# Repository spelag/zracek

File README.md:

# zracek

Spoznajte Zraček – obesek za ključe, ki vam z enim samim pogledom razkrije trenutno kakovost zraka v vaši okolici in 12-urno napoved. Zasnovan je za vse: od tistih, ki jim sodobna tehnologija ni najbližja, do uporabnikov, ki cenijo hitre in preproste rešitve v vsakdanjem življenju. Uporabljate raje pametno uro? Z obrazom za uro Zraček imate podatke vedno na zapestju. Na naši spletni strani pa lahko preverite tudi, kje v okolici so nove merilne postaje najbolj nujne, glede na dejavnike kot so bližina vrtcov, šol in bolnišnic, ter števila uporabnikov Zračka.

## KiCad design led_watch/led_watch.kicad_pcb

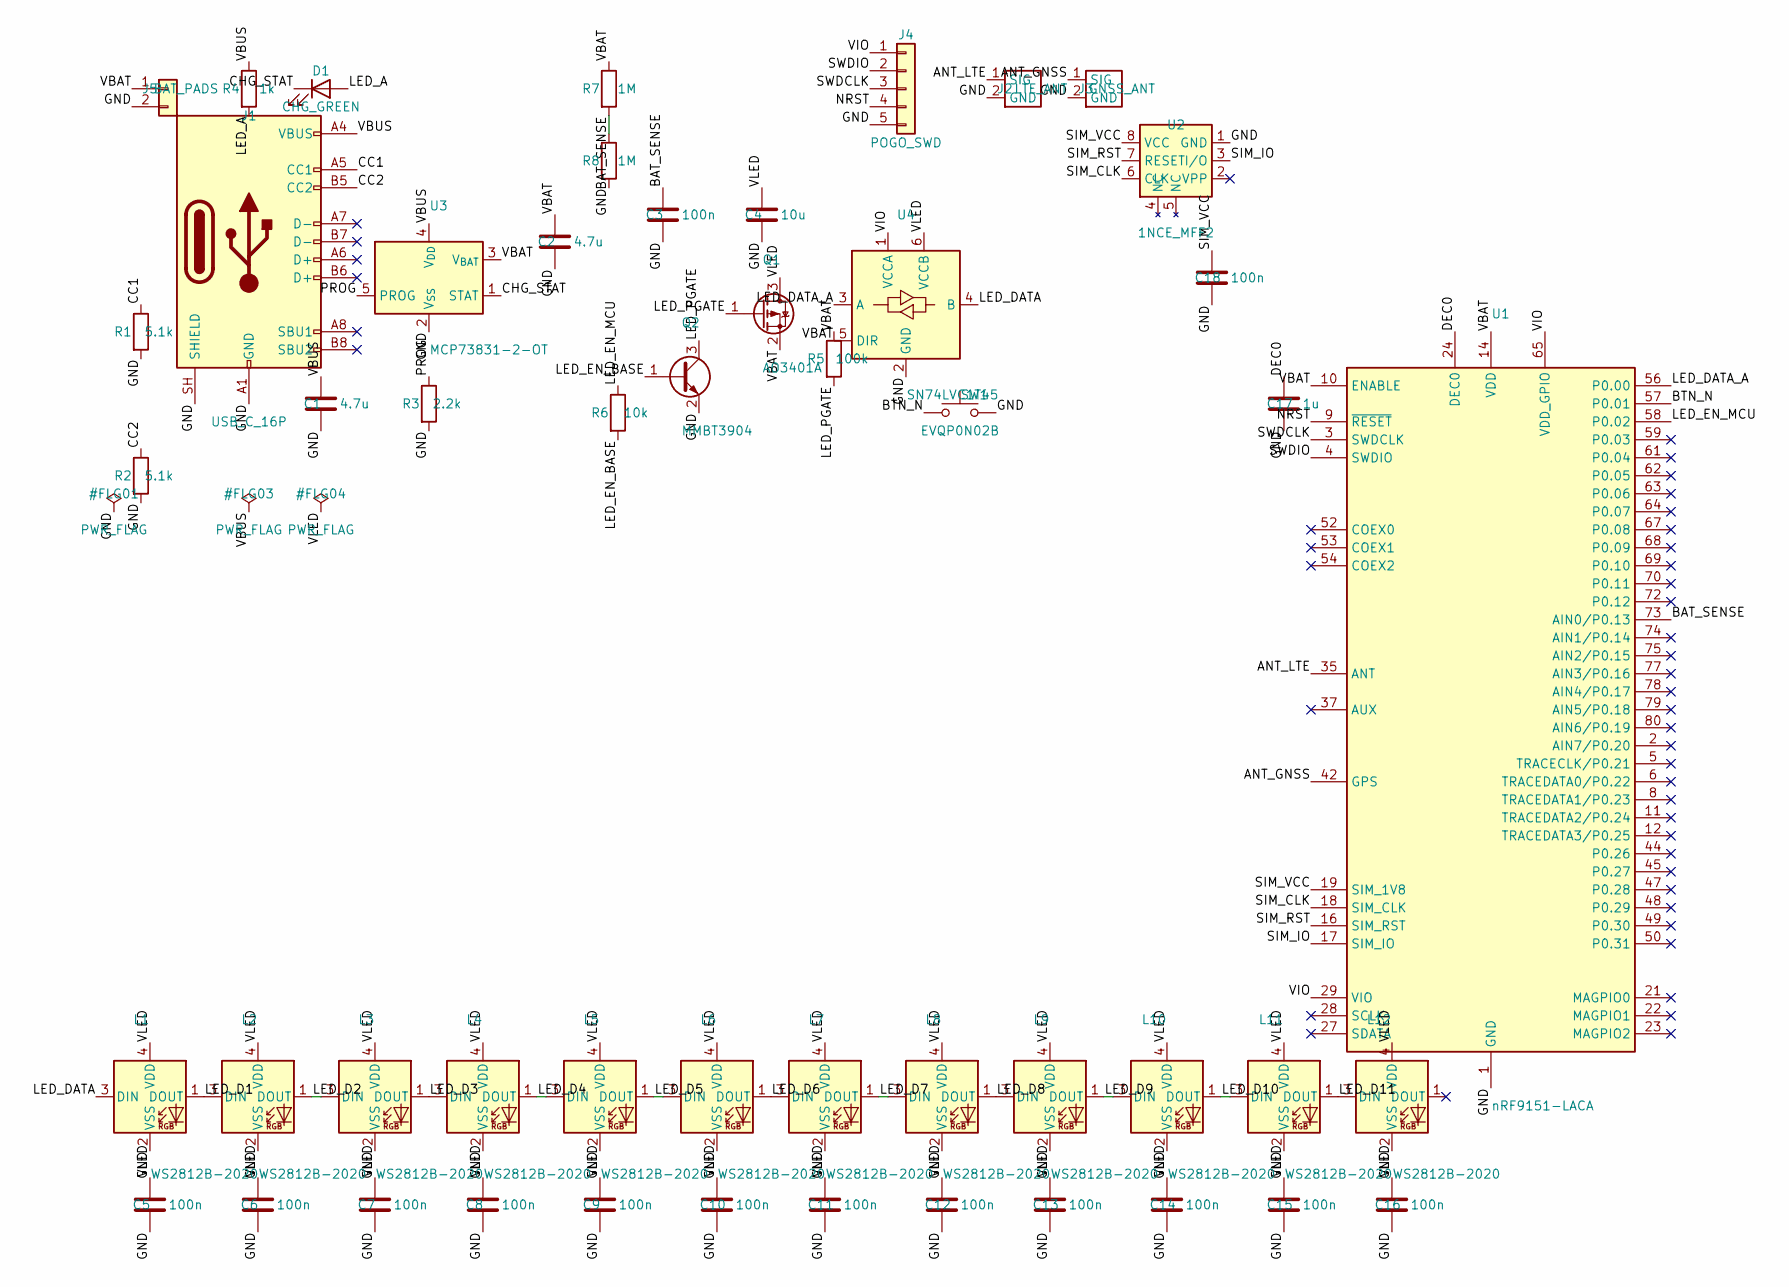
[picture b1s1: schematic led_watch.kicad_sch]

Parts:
C1, C2: 4.7u; C_0603_1608Metric
C3, C5, C6, C7, C8, C9, C10, C11, C12, C13, C14, C15, C16, C18: 100n; C_0402_1005Metric
C4: 10u; C_0603_1608Metric
C17: 1u; C_0402_1005Metric
D1: CHG_GREEN; LED_0603_1608Metric
J1: USB_C_16P; USB_C_Receptacle_HRO_TYPE-C-31-M-12
J2: LTE_ANT; U.FL_Hirose_U.FL-R-SMT-1_Vertical
J3: GNSS_ANT; U.FL_Hirose_U.FL-R-SMT-1_Vertical
J4: POGO_SWD; TestPads_1x05_P1.27mm
J5: BAT_PADS; BatteryPads_2P_P3.0mm
L1, L2, L3, L4, L5, L6, L7, L8, L9, L10, L11, L12: WS2812B-2020; LED_WS2812B-2020_PLCC4_2.0x2.0mm
Q1: AO3401A; SOT-23
Q2: MMBT3904; SOT-23
R1, R2: 5.1k; R_0402_1005Metric
R3: 2.2k; R_0402_1005Metric
R4: 1k; R_0402_1005Metric
R5: 100k; R_0402_1005Metric
R6: 10k; R_0402_1005Metric
R7, R8: 1M; R_0402_1005Metric
SW1: EVQP0N02B; SW_SPST_EVQP0
U1: nRF9151-LACA; Nordic_nRF9151-LAxx_LGA-80-33EP_12.1x11.1mm_P0.5mm
U2: 1NCE_MFF2; MFF2_eSIM
U3: MCP73831-2-OT; SOT-23-5
U4: SN74LVC1T45; SOT-23-6

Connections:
/ANT_GNSS: J3.1 (SIG), U1.42 (GPS)
/ANT_LTE: J2.1 (SIG), U1.35 (ANT)
/BAT_SENSE: C3.1, R7.2, R8.1, U1.73 (AIN0/P0.13)
/BTN_N: SW1.1, U1.57 (P0.01)
/CC1: J1.A5 (CC1), R1.1
/CC2: J1.B5 (CC2), R2.1
/CHG_STAT: D1.1 (K), U3.1 (STAT)
/DEC0: C17.1, U1.24 (DEC0)
/GND: C1.2, C2.2, C3.2, C4.2, C5.2, C6.2, C7.2, C8.2, C9.2, C10.2, C11.2, C12.2, C13.2, C14.2, C15.2, C16.2, C17.2, C18.2, J1.A1 (GND), J1.A12 (GND), J1.B1 (GND), J1.B12 (GND), J1.SH (SHIELD), J2.2 (GND), J3.2 (GND), J4.5, J5.2, L1.2 (VSS), L2.2 (VSS), L3.2 (VSS), L4.2 (VSS), L5.2 (VSS), L6.2 (VSS), L7.2 (VSS), L8.2 (VSS), L9.2 (VSS), L10.2 (VSS), L11.2 (VSS), L12.2 (VSS), Q2.2 (E), R1.2, R2.2, R3.2, R8.2, SW1.2, U1.1 (GND), U1.7 (GND), U1.13 (GND), U1.15 (GND), U1.20 (GND), U1.25 (GND), U1.30 (GND), U1.34 (GND), U1.36 (GND), U1.38 (GND), U1.39 (GND), U1.40 (GND), U1.41 (GND), U1.43 (GND), U1.46 (GND), U1.51 (GND), U1.55 (GND), U1.60 (GND), U1.66 (GND), U1.71 (GND), U1.76 (GND), U1.105 (GND), U1.106 (GND), U1.107 (GND), U1.108 (GND), U1.109 (GND), U1.110 (GND), U1.111 (GND), U1.112 (GND), U1.113 (GND), U2.1 (GND), U3.2 (V_{SS}), U4.2 (GND)
/LED_A: D1.2 (A), R4.2
/LED_D1: L1.1 (DOUT), L2.3 (DIN)
/LED_D2: L2.1 (DOUT), L3.3 (DIN)
/LED_D3: L3.1 (DOUT), L4.3 (DIN)
/LED_D4: L4.1 (DOUT), L5.3 (DIN)
/LED_D5: L5.1 (DOUT), L6.3 (DIN)
/LED_D6: L6.1 (DOUT), L7.3 (DIN)
/LED_D7: L7.1 (DOUT), L8.3 (DIN)
/LED_D8: L8.1 (DOUT), L9.3 (DIN)
/LED_D9: L9.1 (DOUT), L10.3 (DIN)
/LED_D10: L10.1 (DOUT), L11.3 (DIN)
/LED_D11: L11.1 (DOUT), L12.3 (DIN)
/LED_DATA: L1.3 (DIN), U4.4 (B)
/LED_DATA_A: U1.56 (P0.00), U4.3 (A)
/LED_EN_BASE: Q2.1 (B), R6.2
/LED_EN_MCU: R6.1, U1.58 (P0.02)
/LED_PGATE: Q1.1 (G), Q2.3 (C), R5.2
/NRST: J4.4, U1.9 (~RESET)
/PROG: R3.1, U3.5 (PROG)
/SIM_CLK: U1.18 (SIM_CLK), U2.6 (CLK)
/SIM_IO: U1.17 (SIM_IO), U2.3 (I/O)
/SIM_RST: U1.16 (SIM_RST), U2.7 (RESET)
/SIM_VCC: C18.1, U1.19 (SIM_1V8), U2.8 (VCC)
/SWDCLK: J4.3, U1.3 (SWDCLK)
/SWDIO: J4.2, U1.4 (SWDIO)
/VBAT: C2.1, J5.1, Q1.2 (S), R5.1, R7.1, U1.10 (ENABLE), U1.14 (VDD), U3.3 (V_{BAT}), U4.5 (DIR)
/VBUS: C1.1, J1.A4 (VBUS), J1.A9 (VBUS), J1.B4 (VBUS), J1.B9 (VBUS), R4.1, U3.4 (V_{DD})
/VIO: J4.1, U1.29 (VIO), U1.65 (VDD_GPIO), U4.1 (VCCA)
/VLED: C4.1, C5.1, C6.1, C7.1, C8.1, C9.1, C10.1, C11.1, C12.1, C13.1, C14.1, C15.1, C16.1, L1.4 (VDD), L2.4 (VDD), L3.4 (VDD), L4.4 (VDD), L5.4 (VDD), L6.4 (VDD), L7.4 (VDD), L8.4 (VDD), L9.4 (VDD), L10.4 (VDD), L11.4 (VDD), L12.4 (VDD), Q1.3 (D), U4.6 (VCCB)

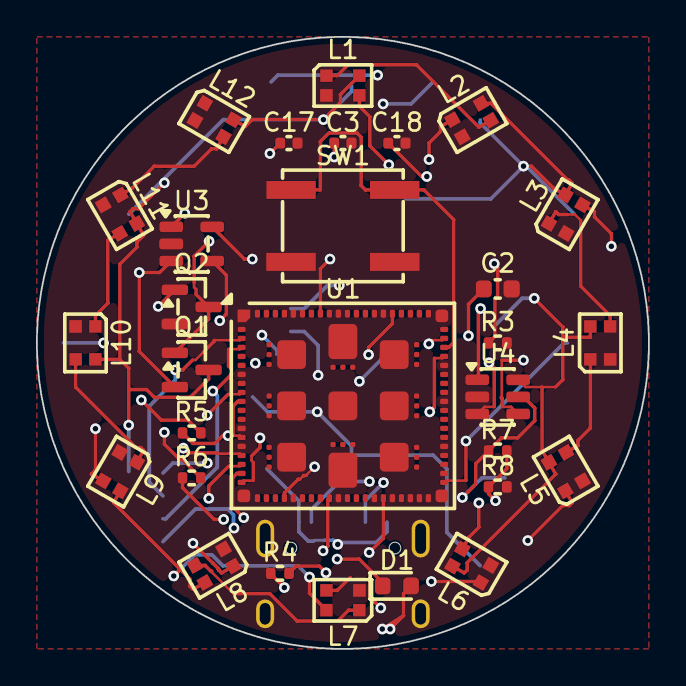
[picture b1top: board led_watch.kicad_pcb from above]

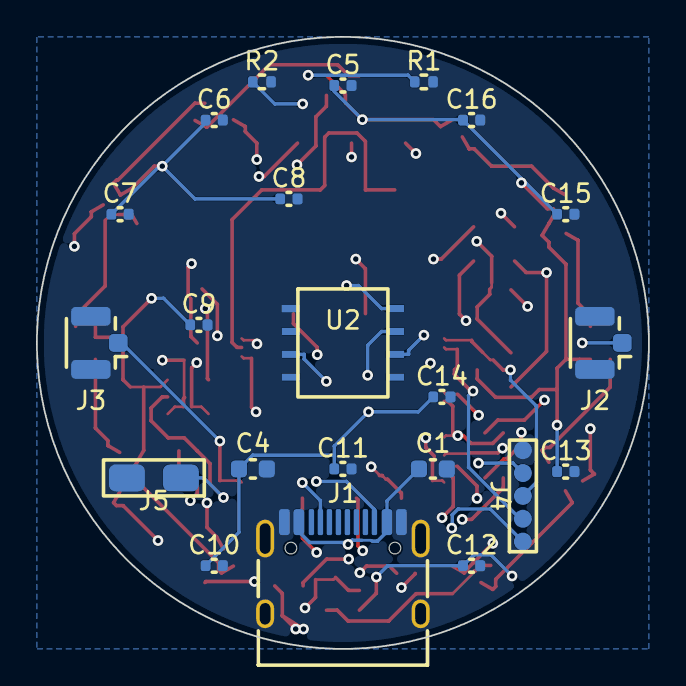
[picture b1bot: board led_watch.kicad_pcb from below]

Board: 4 copper layers, 34.0 x 34.0 mm, 51 parts (22 on the bottom side), 38 nets.

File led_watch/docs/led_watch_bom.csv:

"Reference","Value","Footprint","Description"
"C1","4.7u","Capacitor_SMD:C_0603_1608Metric","Unpolarized capacitor"
"C2","4.7u","Capacitor_SMD:C_0603_1608Metric","Unpolarized capacitor"
"C3","100n","Capacitor_SMD:C_0402_1005Metric","Unpolarized capacitor"
"C4","10u","Capacitor_SMD:C_0603_1608Metric","Unpolarized capacitor"
"C5","100n","Capacitor_SMD:C_0402_1005Metric","Unpolarized capacitor"
"C6","100n","Capacitor_SMD:C_0402_1005Metric","Unpolarized capacitor"
"C7","100n","Capacitor_SMD:C_0402_1005Metric","Unpolarized capacitor"
"C8","100n","Capacitor_SMD:C_0402_1005Metric","Unpolarized capacitor"
"C9","100n","Capacitor_SMD:C_0402_1005Metric","Unpolarized capacitor"
"C10","100n","Capacitor_SMD:C_0402_1005Metric","Unpolarized capacitor"
"C11","100n","Capacitor_SMD:C_0402_1005Metric","Unpolarized capacitor"
"C12","100n","Capacitor_SMD:C_0402_1005Metric","Unpolarized capacitor"
"C13","100n","Capacitor_SMD:C_0402_1005Metric","Unpolarized capacitor"
"C14","100n","Capacitor_SMD:C_0402_1005Metric","Unpolarized capacitor"
"C15","100n","Capacitor_SMD:C_0402_1005Metric","Unpolarized capacitor"
"C16","100n","Capacitor_SMD:C_0402_1005Metric","Unpolarized capacitor"
"C17","1u","Capacitor_SMD:C_0402_1005Metric","Unpolarized capacitor"
"C18","100n","Capacitor_SMD:C_0402_1005Metric","Unpolarized capacitor"
"D1","CHG_GREEN","LED_SMD:LED_0603_1608Metric","Light emitting diode"
"J1","USB_C_16P","Connector_USB:USB_C_Receptacle_HRO_TYPE-C-31-M-12","USB 2.0-only 16P Type-C Receptacle connector"
"J2","LTE_ANT","Connector_Coaxial:U.FL_Hirose_U.FL-R-SMT-1_Vertical","U.FL / IPEX MHF1 coaxial antenna connector"
"J3","GNSS_ANT","Connector_Coaxial:U.FL_Hirose_U.FL-R-SMT-1_Vertical","U.FL / IPEX MHF1 coaxial antenna connector"
"J4","POGO_SWD","led_watch:TestPads_1x05_P1.27mm","Generic connector, single row, 01x05, script generated (kicad-library-utils/schlib/autogen/connector/)"
"J5","BAT_PADS","led_watch:BatteryPads_2P_P3.0mm","Generic connector, single row, 01x02, script generated (kicad-library-utils/schlib/autogen/connector/)"
"L1","WS2812B-2020","LED_SMD:LED_WS2812B-2020_PLCC4_2.0x2.0mm","RGB LED with integrated controller, 2.0 x 2.0 mm, 12 mA"
"L2","WS2812B-2020","LED_SMD:LED_WS2812B-2020_PLCC4_2.0x2.0mm","RGB LED with integrated controller, 2.0 x 2.0 mm, 12 mA"
"L3","WS2812B-2020","LED_SMD:LED_WS2812B-2020_PLCC4_2.0x2.0mm","RGB LED with integrated controller, 2.0 x 2.0 mm, 12 mA"
"L4","WS2812B-2020","LED_SMD:LED_WS2812B-2020_PLCC4_2.0x2.0mm","RGB LED with integrated controller, 2.0 x 2.0 mm, 12 mA"
"L5","WS2812B-2020","LED_SMD:LED_WS2812B-2020_PLCC4_2.0x2.0mm","RGB LED with integrated controller, 2.0 x 2.0 mm, 12 mA"
"L6","WS2812B-2020","LED_SMD:LED_WS2812B-2020_PLCC4_2.0x2.0mm","RGB LED with integrated controller, 2.0 x 2.0 mm, 12 mA"
"L7","WS2812B-2020","LED_SMD:LED_WS2812B-2020_PLCC4_2.0x2.0mm","RGB LED with integrated controller, 2.0 x 2.0 mm, 12 mA"
"L8","WS2812B-2020","LED_SMD:LED_WS2812B-2020_PLCC4_2.0x2.0mm","RGB LED with integrated controller, 2.0 x 2.0 mm, 12 mA"
"L9","WS2812B-2020","LED_SMD:LED_WS2812B-2020_PLCC4_2.0x2.0mm","RGB LED with integrated controller, 2.0 x 2.0 mm, 12 mA"
"L10","WS2812B-2020","LED_SMD:LED_WS2812B-2020_PLCC4_2.0x2.0mm","RGB LED with integrated controller, 2.0 x 2.0 mm, 12 mA"
"L11","WS2812B-2020","LED_SMD:LED_WS2812B-2020_PLCC4_2.0x2.0mm","RGB LED with integrated controller, 2.0 x 2.0 mm, 12 mA"
"L12","WS2812B-2020","LED_SMD:LED_WS2812B-2020_PLCC4_2.0x2.0mm","RGB LED with integrated controller, 2.0 x 2.0 mm, 12 mA"
"Q1","AO3401A","Package_TO_SOT_SMD:SOT-23","-4.0A Id, -30V Vds, P-Channel MOSFET, SOT-23"
"Q2","MMBT3904","Package_TO_SOT_SMD:SOT-23","0.2A Ic, 40V Vce, Small Signal NPN Transistor, SOT-23"
"R1","5.1k","Resistor_SMD:R_0402_1005Metric","Resistor"
"R2","5.1k","Resistor_SMD:R_0402_1005Metric","Resistor"
"R3","2.2k","Resistor_SMD:R_0402_1005Metric","Resistor"
"R4","1k","Resistor_SMD:R_0402_1005Metric","Resistor"
"R5","100k","Resistor_SMD:R_0402_1005Metric","Resistor"
"R6","10k","Resistor_SMD:R_0402_1005Metric","Resistor"
"R7","1M","Resistor_SMD:R_0402_1005Metric","Resistor"
"R8","1M","Resistor_SMD:R_0402_1005Metric","Resistor"
"SW1","EVQP0N02B","Button_Switch_SMD:SW_SPST_EVQP0","Push button switch, generic, two pins"
"U1","nRF9151-LACA","Package_LGA:Nordic_nRF9151-LAxx_LGA-80-33EP_12.1x11.1mm_P0.5mm","Low power SiP with integrated LTE-M/NB-IoT and DECT NR+ modem, and GNSS, 1.7..5.5V, 1 MB flash, 256 kB RAM,  LGA-80-33EP"
"U2","1NCE_MFF2","led_watch:MFF2_eSIM","MFF2 / QFN-8 industrial eSIM (1NCE IoT SIM Chip Industrial), 5 x 6 mm, 1.27 mm pitch"
"U3","MCP73831-2-OT","Package_TO_SOT_SMD:SOT-23-5","Single cell, Li-Ion/Li-Po charge management controller, 4.20V, Tri-State Status Output, in SOT23-5 package"
"U4","SN74LVC1T45","Package_TO_SOT_SMD:SOT-23-6","Single-Bit Dual-Supply Bus Transceiver With Configurable Voltage Translation and 3-State Outputs, SOT-23-6"
